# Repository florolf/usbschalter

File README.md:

# Purpose

In our hackerspace [RFID dooropener project](https://github.com/entropia/tuerd),
we encountered the problem that the RFID reader would randomly lock up so badly
that only disconnecting and reconnecting it to USB would help. While locking
up could be detected in software, nothing could be done except sending out an
alert and hoping that someone would manually powercycle the reader. This project
attempts to fix this. It allows another piece of software to physically
disconnect and reconnect an USB device.

# Usage

The daemon is meant to be run by some service supervision scheme like
daemontools or [runit](http://smarden.org/runit/). It attaches itself to the
FTDI device (should you have more than one FTDI device present, you'll probably
have to change the VID/PID of one of them to disambiguate) and waits for one of
the following signals in a loop:

* <code>SIGUSR1</code> will turn the device on
* <code>SIGUSR2</code> will turn the device off
* <code>SIGHUP</code> will turn the device off, wait 2 seconds and turn the
  device on again

When the daemon is started, the device will be turned on.

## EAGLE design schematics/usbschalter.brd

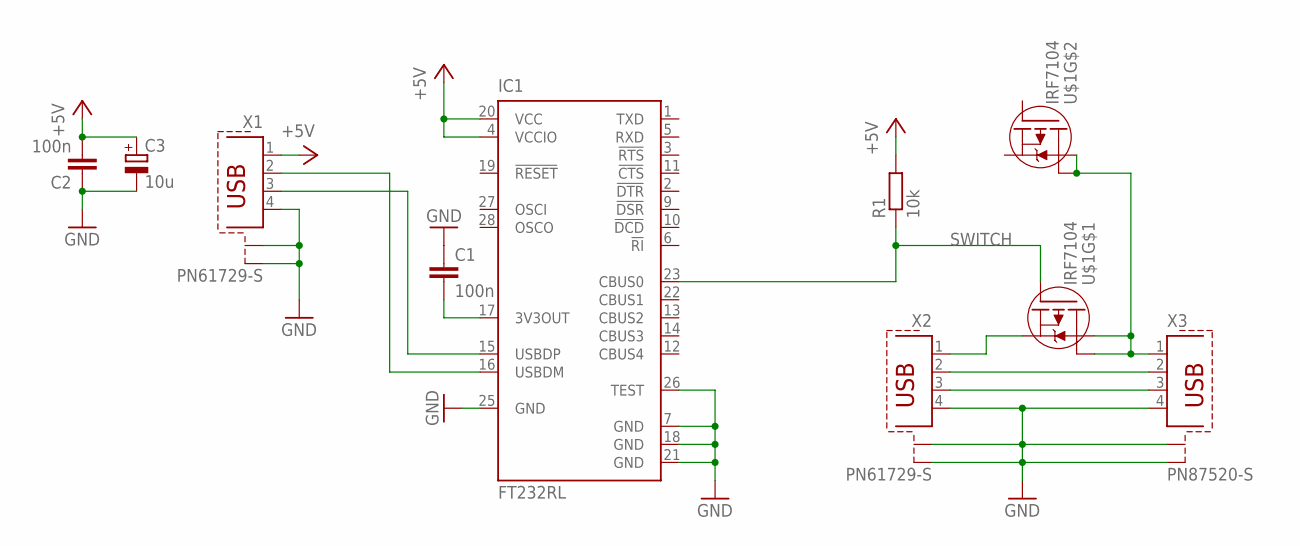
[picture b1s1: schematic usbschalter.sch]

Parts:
C1, C2: 100n; C0805
C3: 10u; E1,8-4
IC1: FT232RL; SSOP28
R1: 10k; R0805
U$1: IRF7104; SO8-2
X1, X2: PN61729-S
X3: PN87520-S

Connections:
+5V: C2.2, C3.+, IC1.4 (VCCIO), IC1.20 (VCC), R1.2, X1.1
GND: C1.1, C2.1, C3.-, IC1.7 (GND), IC1.18 (GND), IC1.21 (GND), IC1.25 (GND), IC1.26 (TEST), X1.4, X1.S1, X1.S2, X2.4, X2.S1, X2.S2, X3.4, X3.S1, X3.S2
unnamed: X2.3, X3.3
unnamed: X2.2, X3.2
unnamed: U$1.1 (S), X2.1
unnamed: IC1.16 (USBDM), X1.2
unnamed: IC1.15 (USBDP), X1.3
unnamed: U$1.5 (D), U$1.6 (D), U$1.7 (D), U$1.8 (D), X3.1
unnamed: C1.2, IC1.17 (3V3OUT)
SWITCH: IC1.23 (CBUS0), R1.1, U$1.2 (G)

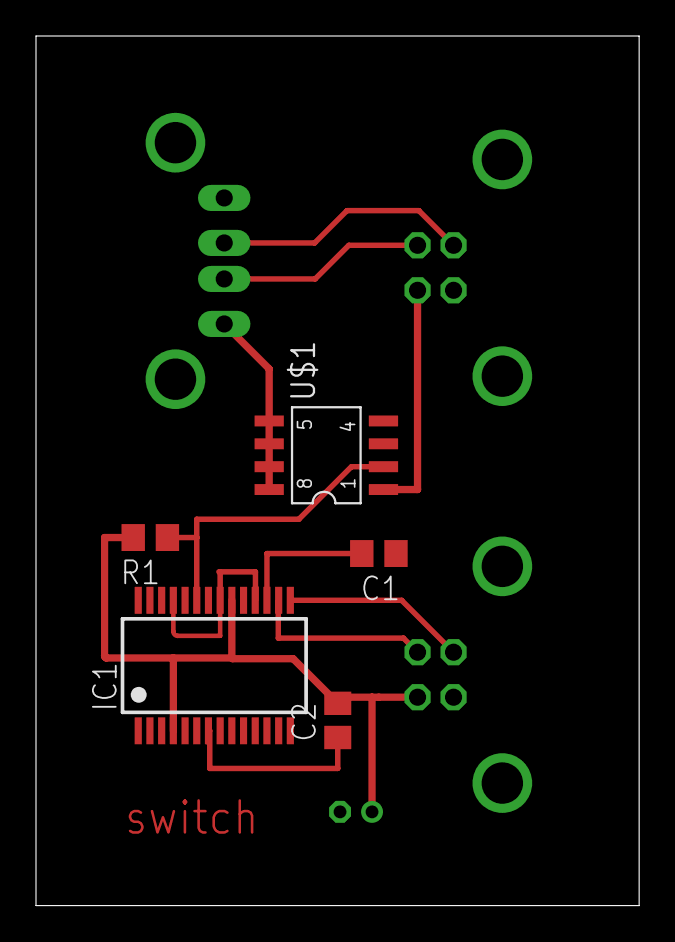
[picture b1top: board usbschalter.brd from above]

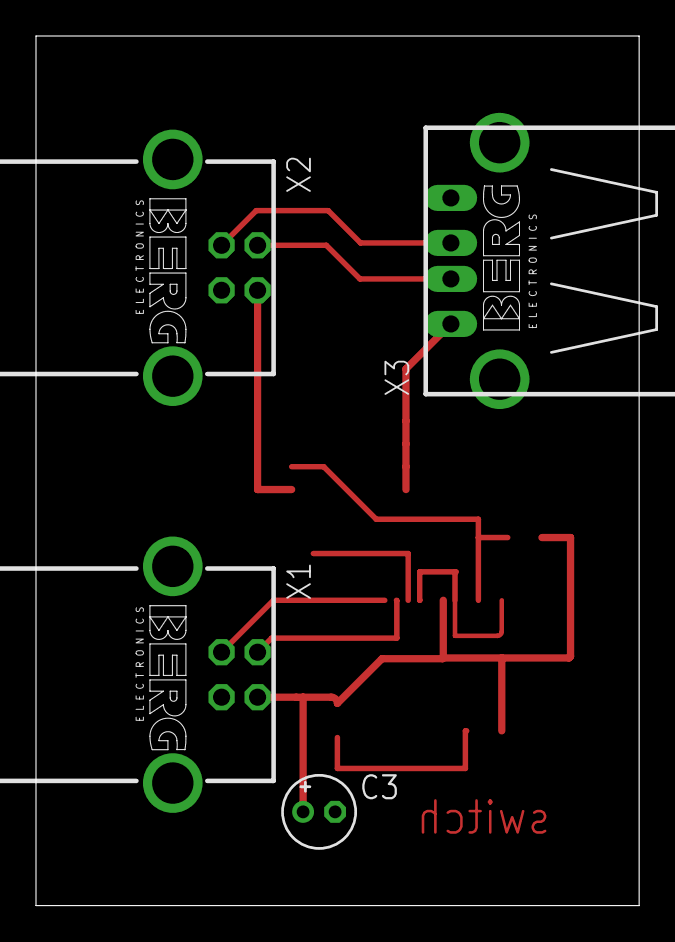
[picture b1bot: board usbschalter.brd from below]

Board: 2 copper layers, 33.5 x 48.3 mm, 9 parts (4 on the bottom side), 10 nets.

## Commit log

2013-09-21 initial import

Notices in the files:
parts and their libraries:
irf-2: Copyright & License
This library is licensed under the General Public License, Version 2.
More Information about the General Public License is available at http://www.gnu.org/copyleft/gpl.html.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
